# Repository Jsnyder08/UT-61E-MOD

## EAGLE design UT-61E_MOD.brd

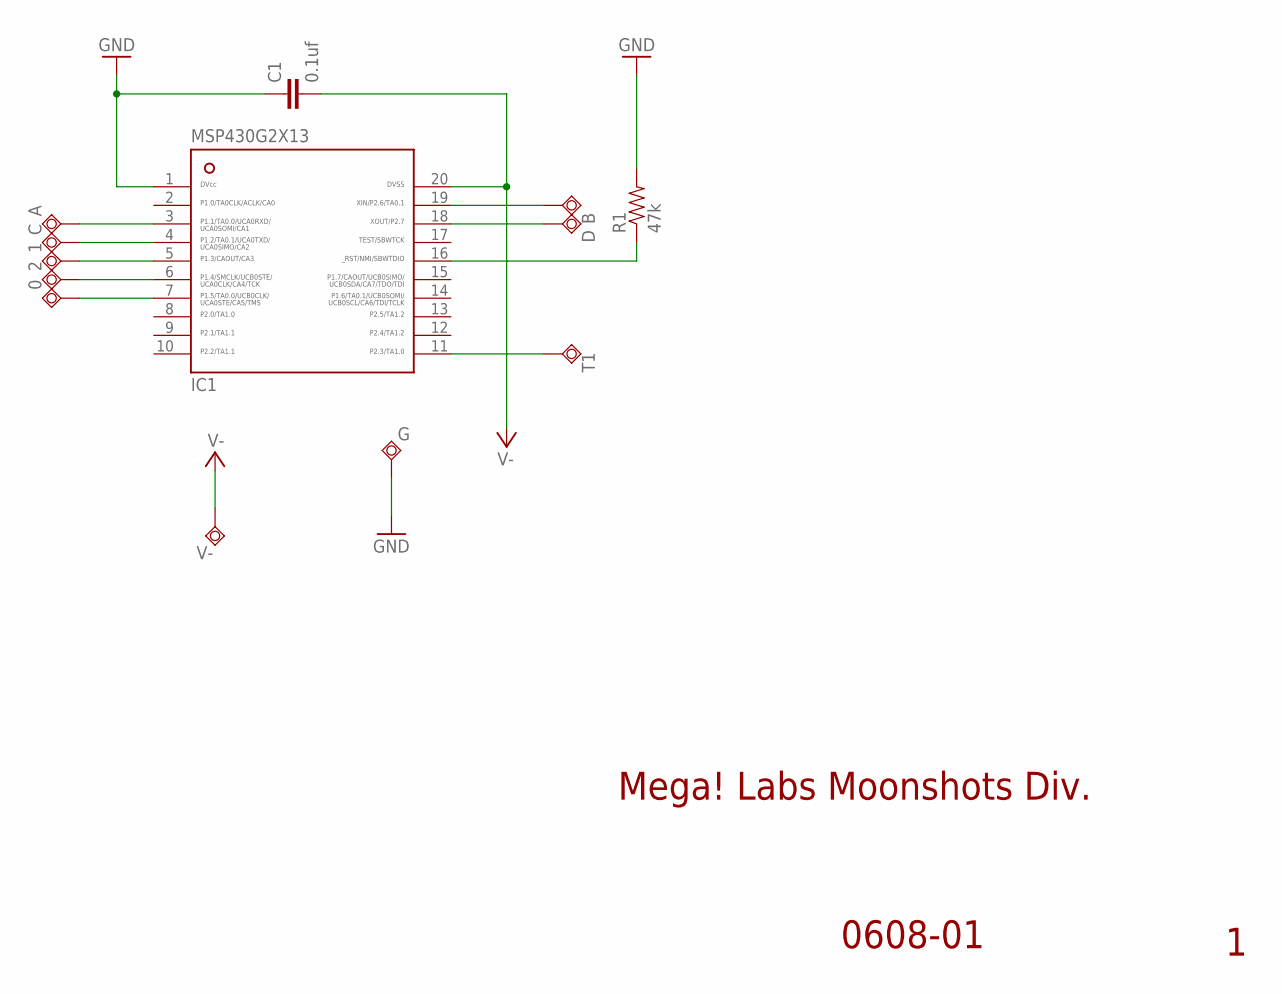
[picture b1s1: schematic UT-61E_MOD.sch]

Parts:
0, 1, 2: TPSQTP18SQ; TP18SQ
A: TPSQTP18SQ; TP18SQ
B: TPSQTP18SQ; TP18SQ
C: TPSQTP18SQ; TP18SQ
C1: 0.1uf; 0805
D: TPSQTP18SQ; TP18SQ
G: TPSQTP18SQ; TP18SQ
IC1: MSP430G2X13-20PW20; PW20
R1: 47k; 0805
T1: TPSQTP18SQ; TP18SQ
V-: TPSQTP18SQ; TP18SQ

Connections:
GND: C1.1, G.TP, IC1.1, R1.2
unnamed: B.TP, IC1.19
unnamed: A.TP, IC1.3
unnamed: C.TP, IC1.4
unnamed: D.TP, IC1.18
unnamed: IC1.16, R1.1
unnamed: 1.TP, IC1.5
unnamed: 2.TP, IC1.6
unnamed: 0.TP, IC1.7
unnamed: IC1.11, T1.TP
V-: C1.2, IC1.20, V-.TP

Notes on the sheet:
Mega! Labs Moonshots Div.
0608-01

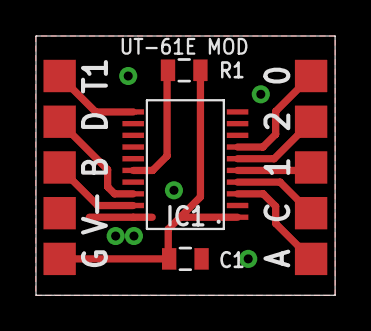
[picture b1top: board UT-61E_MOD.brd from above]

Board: 2 copper layers, 16.6 x 14.4 mm, 13 parts (0 on the bottom side), 11 nets.

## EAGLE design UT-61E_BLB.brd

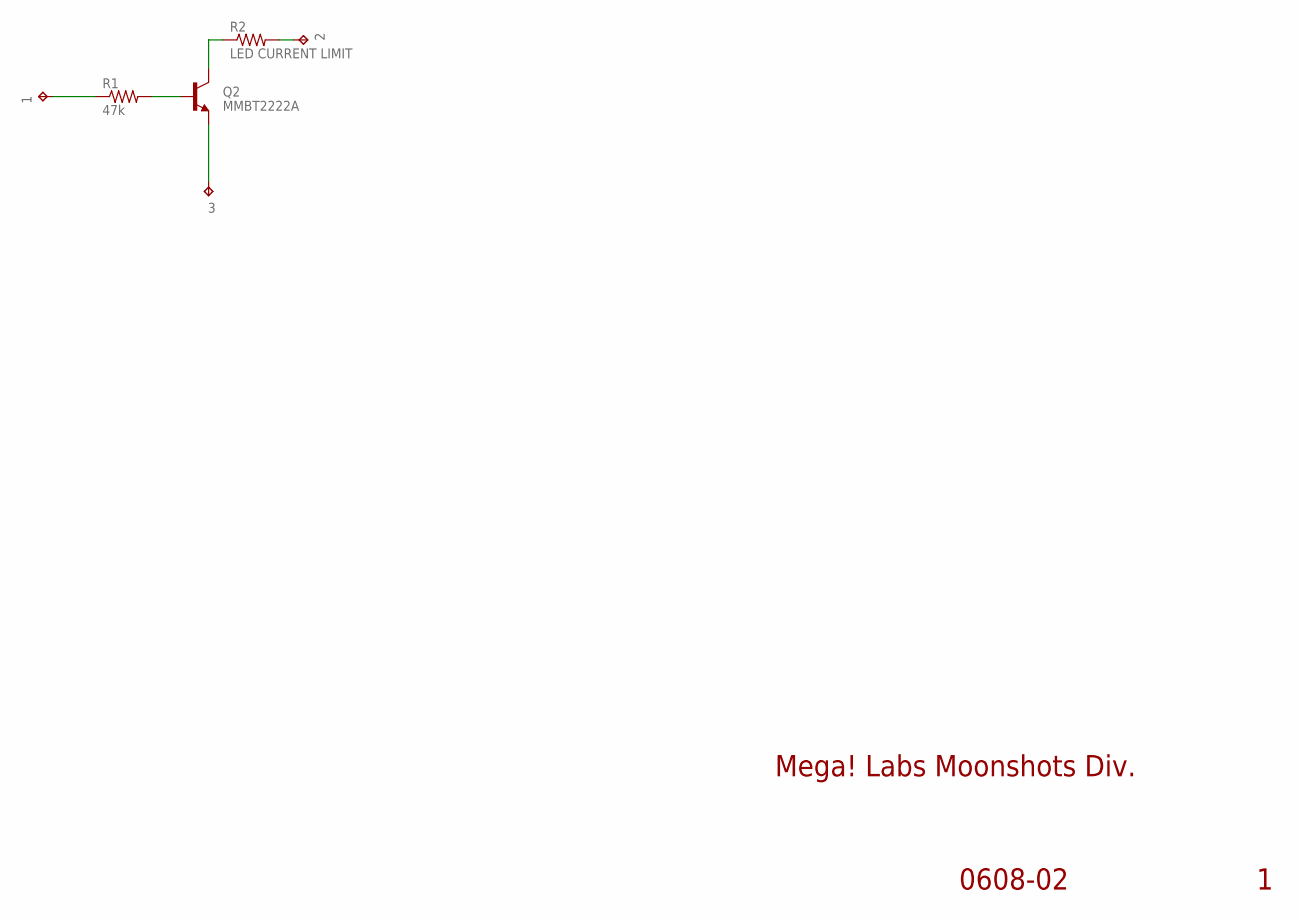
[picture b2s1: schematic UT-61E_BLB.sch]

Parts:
1, 2, 3: TPTP18SQ; TP18SQ
Q2: MMBT2222A; SOT23-3
R1: 47k; 0805
R2: LED CURRENT LIMIT; 0805

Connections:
GND: 3.TP, Q2.2 (E)
unnamed: Q2.1 (B), R1.2
unnamed: 1.TP, R1.1
unnamed: Q2.3 (C), R2.1
unnamed: 2.TP, R2.2

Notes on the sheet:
Mega! Labs Moonshots Div.
0608-02

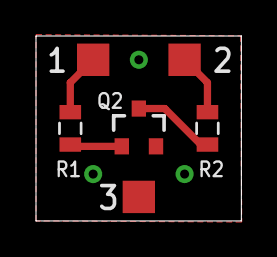
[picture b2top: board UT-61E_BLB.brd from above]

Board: 2 copper layers, 11.4 x 10.3 mm, 6 parts (0 on the bottom side), 5 nets.

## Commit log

2015-11-12 :space_invader: Added .gitattributes & .gitignore files
2015-11-12 UT-61E Mod Chip
    UT-61E Mod chip to enable extra features / backlight

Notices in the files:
parts and their libraries:
SparkFun-DiscreteSemi: Licensing: Creative Commons ShareAlike 4.0 International - https://creativecommons.org/licenses/by-sa/4.0
